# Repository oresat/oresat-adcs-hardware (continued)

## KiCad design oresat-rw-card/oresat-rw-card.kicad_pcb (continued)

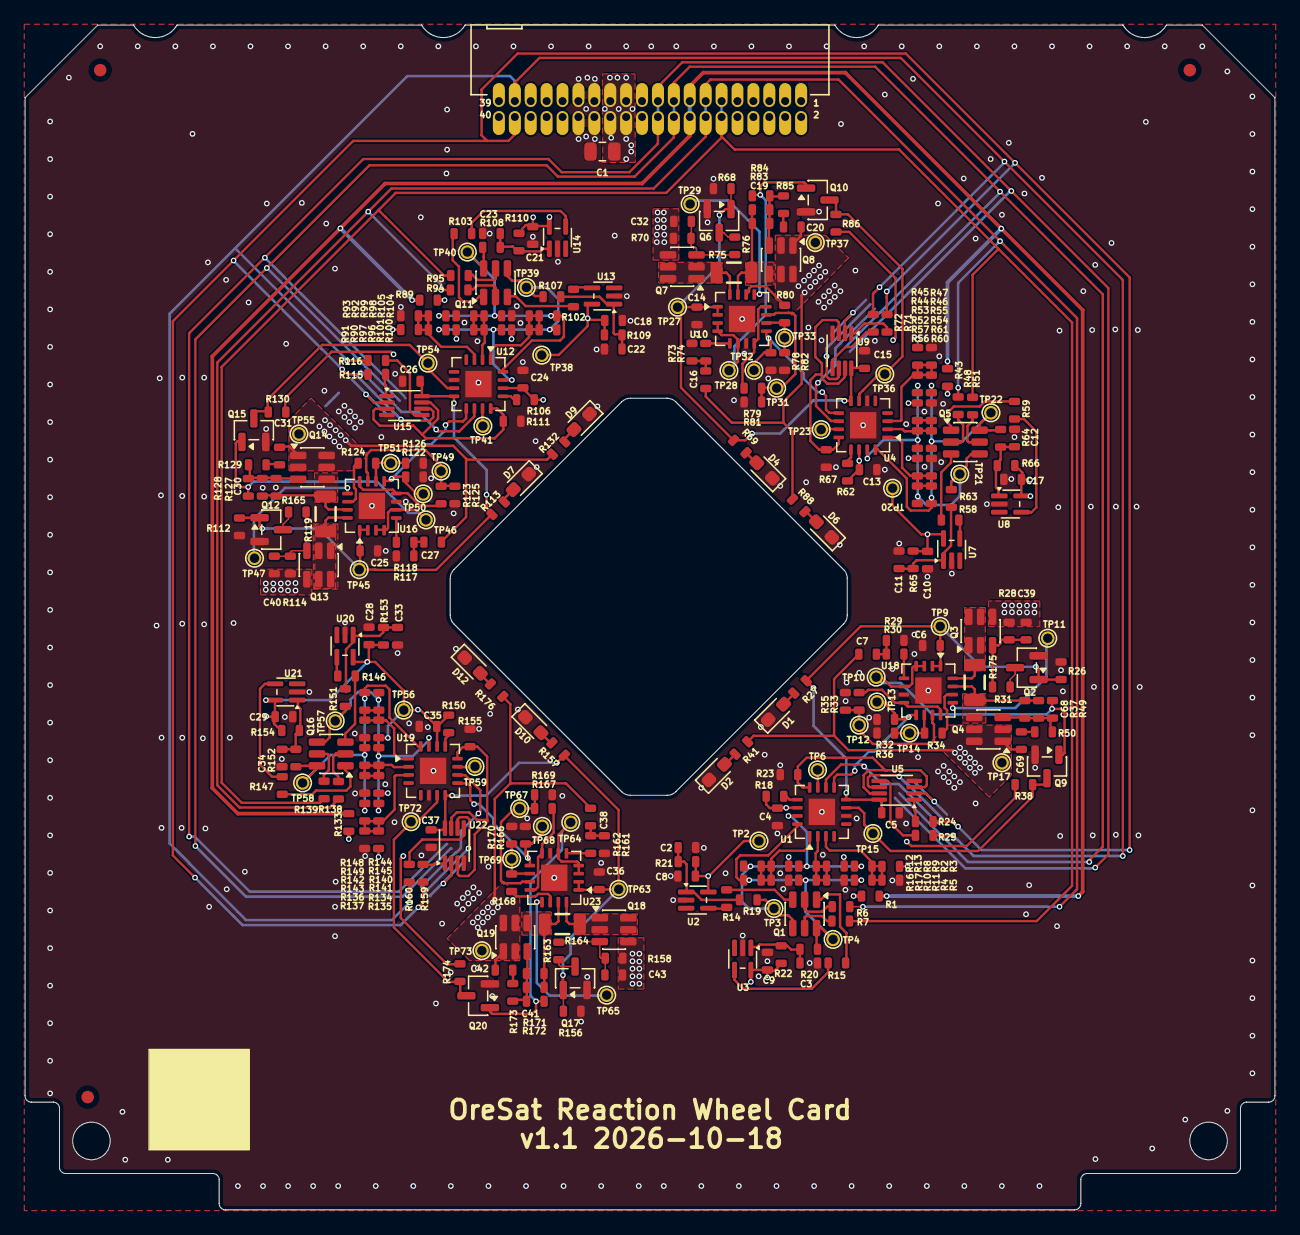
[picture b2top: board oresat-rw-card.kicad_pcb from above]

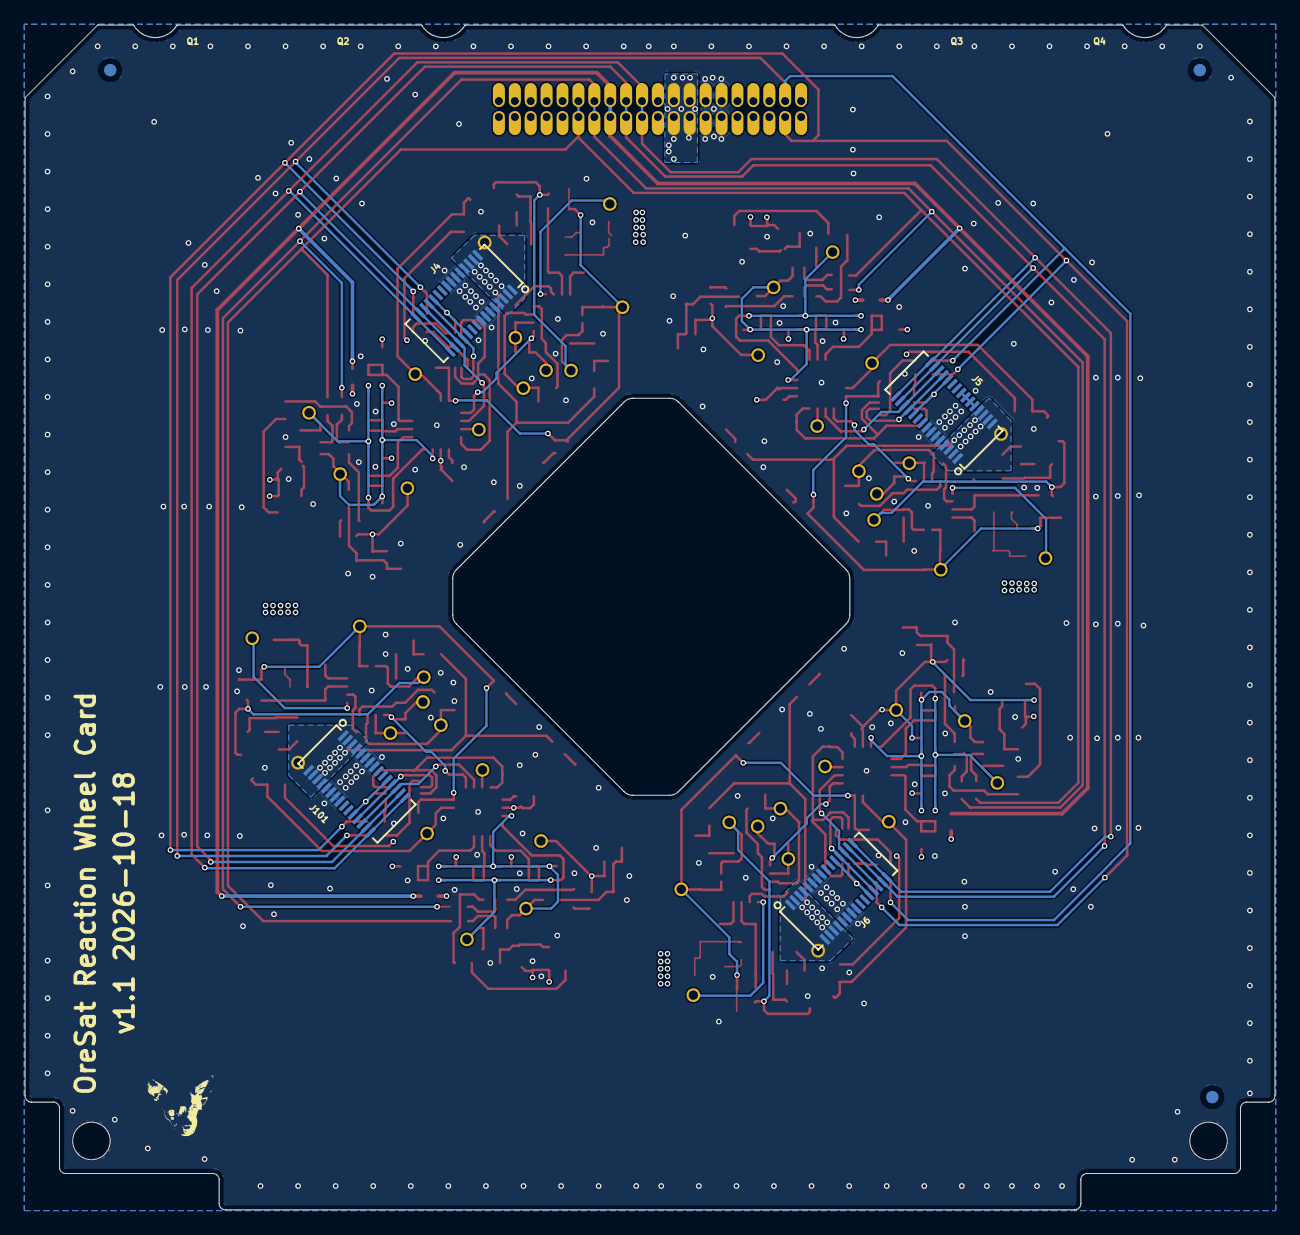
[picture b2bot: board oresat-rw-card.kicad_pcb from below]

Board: 4 copper layers, 99.8 x 94.6 mm, 321 parts (7 on the bottom side), 178 nets.

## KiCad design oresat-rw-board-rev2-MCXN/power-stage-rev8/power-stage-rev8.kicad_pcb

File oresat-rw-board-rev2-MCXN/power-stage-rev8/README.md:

---
title: "**MCXN-Reaction-Wheel-Board-V2**"
subtitle: |
  **Fabrication and Assembly Information**\
  For build TIME-STAMP
fontsize: 10pt
geometry:
  - margin=0.5in
toc: true
toc-depth: 2
colorlinks: true
urlcolor: blue
---

\newpage

# About this Board

## Board Description

The MCXN-Reaction-Wheel-Board-V2 is the dedicated controller board for the reaction wheel assembly. Each controller manages a single reaction wheel. Centered around the NXP MCXN947VDFT microcontroller, this board combines:

- GaN H-bridge inverters for motor driving
- Current sense amplifiers
- Encoder interfacing
- Additional thermal and voltage metrology
- Communication to the ADCS Card

## Documentation Links

- ADCS hardware Git repository: <https://github.com/oresat/oresat-adcs-hardware>

## Documentation Files

| Filename                        | Notes                                    |
| ------------------------------- | ---------------------------------------- |
| README.pdf                      | This README file                         |
| PROJECT-NAME-outline.dxf        | Board outline (with holes) in DXF format |
| PROJECT-NAME-pcba.step          | 3D model of PCBA (with components)       |
| PROJECT-NAME-render-top.jpg     | Render of the top of the 3D model        |
| PROJECT-NAME-render-bot.jpg     | Render of the bottom of the 3D model     |
| PROJECT-NAME-schematic.pdf      | PDF of board schematics                  |

## Board Renders

{width=50%}
{width=50%}

\newpage

# Printed Circuit Board (PCB) Fabrication Information

## Board Info

- 6-layer board
- Bounding box is approximately 50 x 33.5 mm 
- Board thickness is 1.6 mm 
- **Important:** See Materials section below
- 
## Board Requirements

- Design Rules
    - Minimum Trace width: 0.1 mm
    - Minimum Clearance/Space: 0.1 mm
- Drills and Vias
   - Via Diameter: 0.20 mm
   - Minimum Annular Width: 0.07 mm
- Outline/Routing
  - Requires a routing bit suitable for the 50x33.5mm profile.
- If not otherwise specified, build to IPC 6012 Class 2 or better. High precision is required across all fabrication steps.

## Materials

- Dielectric Material: Standard FR4
- Board Surface Treatment: ENIG (Electroless Nickel Immersion Gold)
- Controlled Impedance: None required

## Fabrication Files

### IPC-2581 File

| Filename                 | Notes                                   |
| ------------------------ | --------------------------------------- |
| PROJECT-NAME-ipc2581.xml | IPC-2581 board information file         |

### Legacy PCB Files (Gerbers/Drills)

| Filename                      | Notes                                         |
| ------------------------------| --------------------------------------------- |
| PROJECT-NAME-Edge_Cuts.gbr    | RS274X file for the dimension (outline) layer |
| PROJECT-NAME-F_Silkscreen.gbr | RS274X file for the top silkscreen            |
| PROJECT-NAME-F_Mask.gbr       | RS274X file for the top soldermask            |
| PROJECT-NAME-F_Cu.gbr         | RS274X file for the top copper layer          |
| PROJECT-NAME-In1_Cu.gbr       | RS274X file for the layer 2 copper            |
| PROJECT-NAME-In2_Cu.gbr       | RS274X file for the layer 3 copper            |
| PROJECT-NAME-In3_Cu.gbr       | RS274X file for the layer 4 copper            |
| PROJECT-NAME-In4_Cu.gbr       | RS274X file for the layer 5 copper            |
| PROJECT-NAME-B_Cu.gbr         | RS274X file for the bottom copper layer       |
| PROJECT-NAME-B_Mask.gbr       | RS274X file for the bottom soldermask         |
| PROJECT-NAME-B_Silkscreen.gbr | RS274X file for the bottom silkscreen         |
| PROJECT-NAME-NPTH.drl         | Excellon file for non-plated through holes    |
| PROJECT-NAME-PTH.drl          | Excellon file for plated through holes        | 

\newpage

# Printed Circuit Board Assembly (PCBA) Information

## Assembly Info

- Double-sided assembly (components on both Top and Bottom sides).
- Exclusively Surface Mount Technology (SMT) components; no Through-Hole (THT) parts.

## Assembly Requirements

- **Precision:** Extreme precision is required for all placement and reflow operations due to the density and component types (GaN, MCXN947VDFT).
- Assemble to IPC Class 2 or better.
- Solder paste **MUST** be leaded.
- Aqueous flux and wash strongly preferred.
   - Clean to NASA Standard "Visibly Clean (VC)": No particles or residues are visible to the naked eye.
- Ship in antistatic protective bags.

## Assembly Files

### IPC-2581 File

| Filename                 | Notes                           |
| ------------------------ | ------------------------------- |
| PROJECT-NAME-ipc2581.xml | IPC-2581 board information file |

### Bill of Materials (BOM)

| Filename             | Description                            |
| -------------------- | -------------------------------------- |
| PROJECT-NAME-bom.csv | BOM in Comma Separated Variable format |

### Solder Paste Stencils

| Filename                 | Notes                                            |
| ------------------------ | ------------------------------------------------ |
| PROJECT-NAME-B_Paste.gbr | RS274X file for bottom/back solder paste stencil |
| PROJECT-NAME-F_Paste.gbr | RS274X file for top/front solder paste stencil   |

### Mounting/Placement Location

| Filename            | Description                                 |
| ------------------- | ------------------------------------------- |
| PROJECT-NAME.pos    | Pick and place locations for components     |

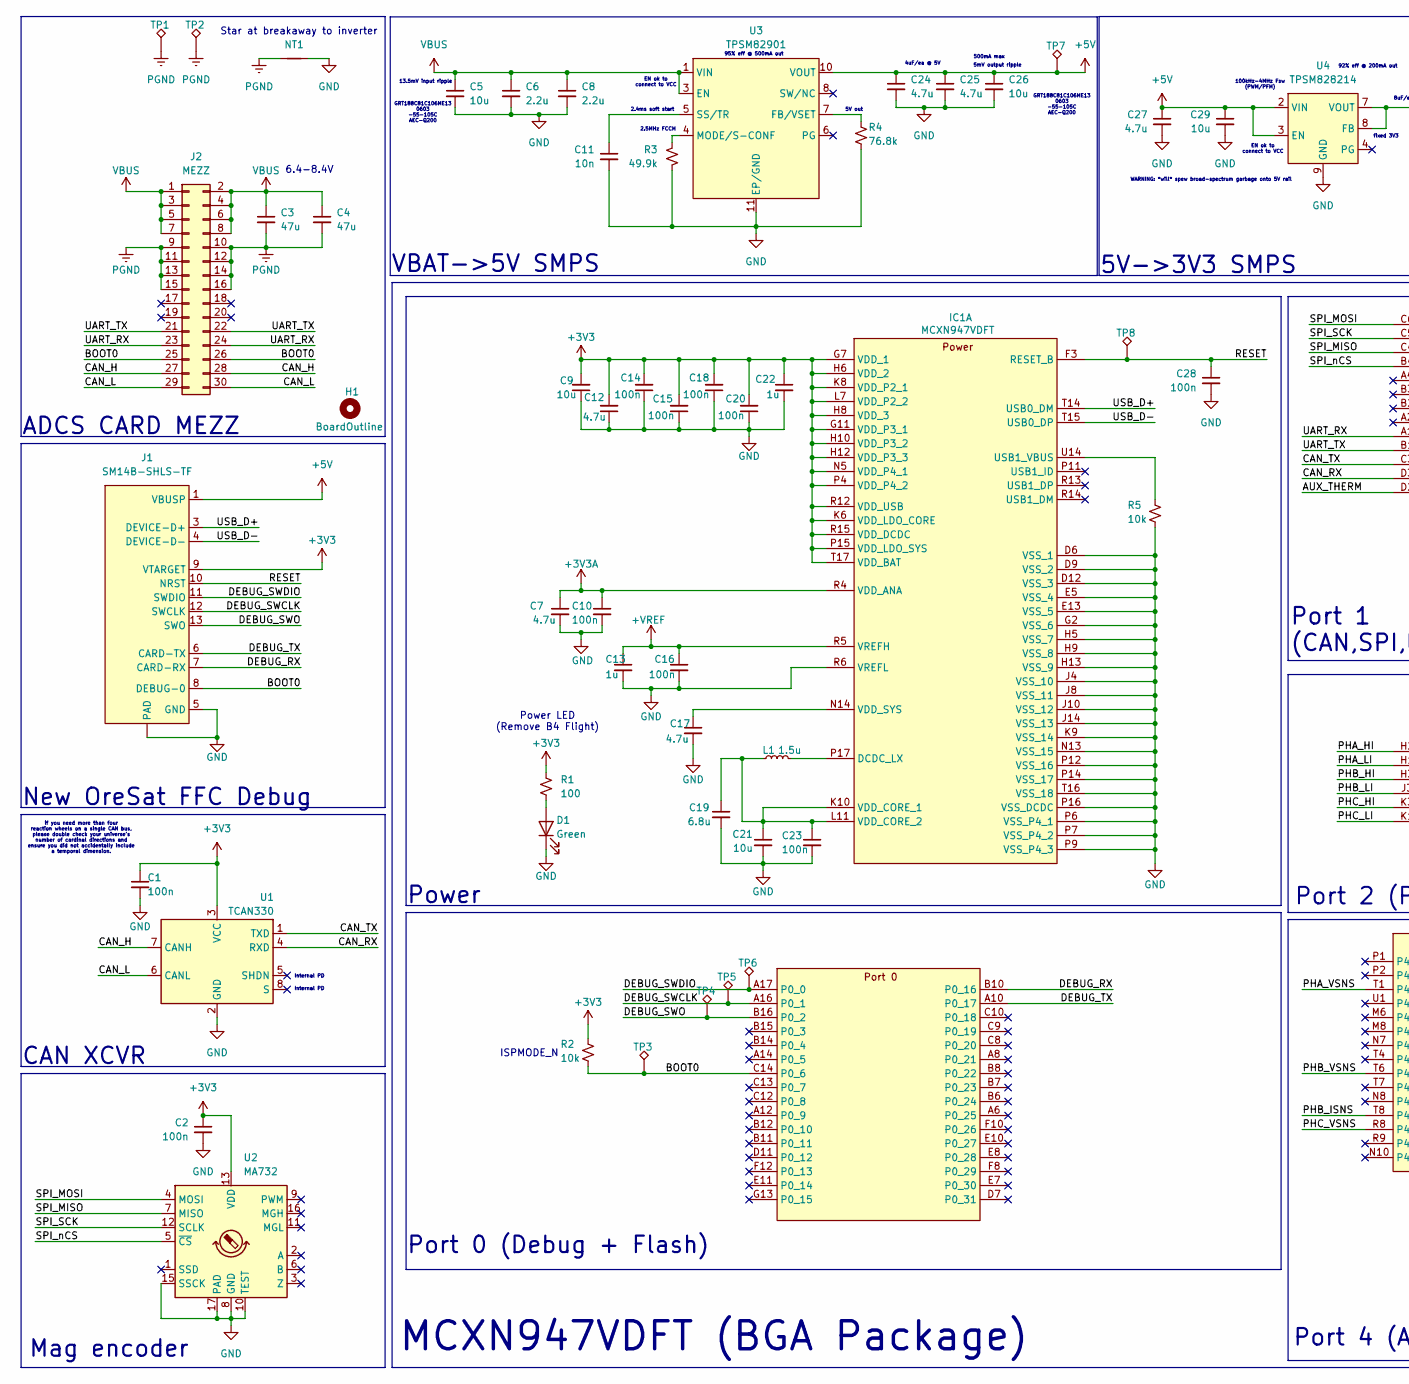
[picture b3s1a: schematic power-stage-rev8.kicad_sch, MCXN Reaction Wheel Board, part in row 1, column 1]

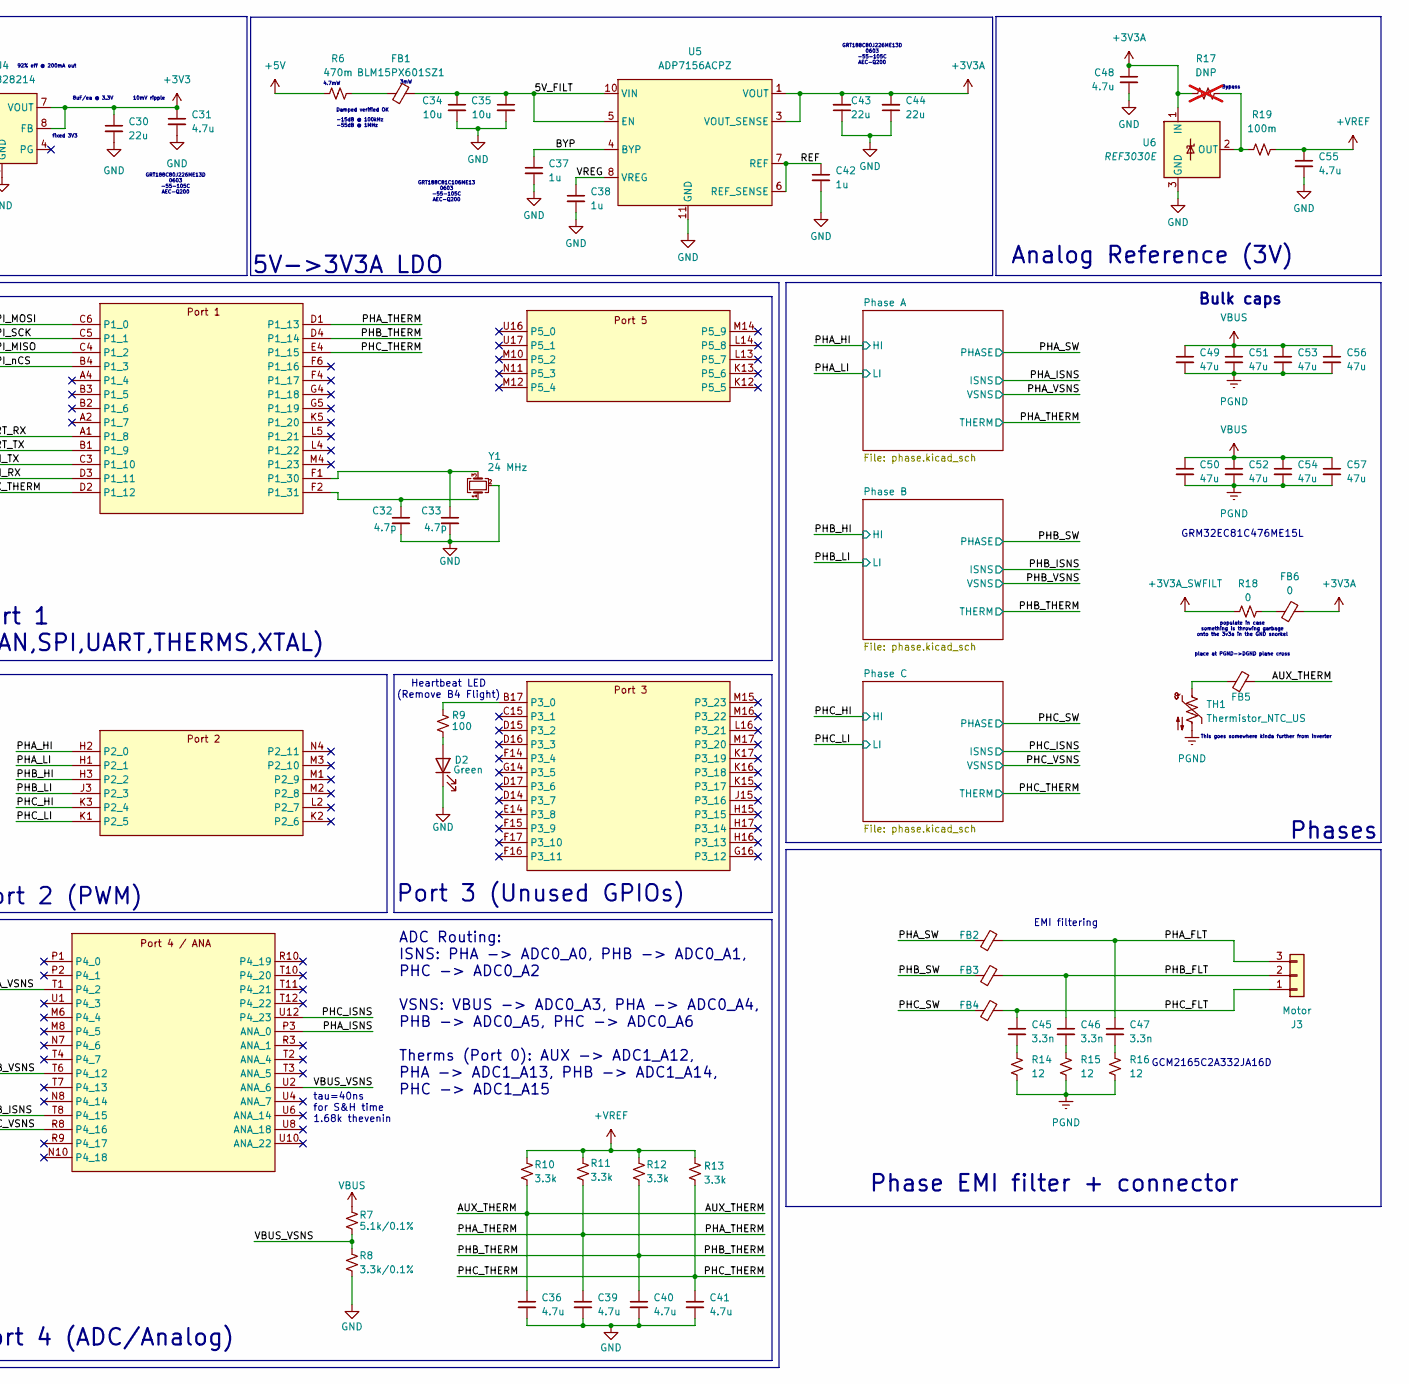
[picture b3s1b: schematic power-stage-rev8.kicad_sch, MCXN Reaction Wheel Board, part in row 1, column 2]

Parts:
C1, C2, C10, C14, C15, C16, C18, C20, C23, C28: 100n; C_0402_1005Metric; MPN GRT155R71E104KE01J
C3, C4, C49, C50, C51, C52, C53, C54, C56, C57: 47u; C_1210_3225Metric; MPN GRT32EC81C476KE13L
C5, C9, C21, C26, C29, C34, C35: 10u; C_0603_1608Metric; MPN GRT188C81C106ME13D
C6, C8: 2.2u; C_0402_1005Metric; MPN GRT155C81C225ME13D
C7, C12, C17, C24, C25, C27, C31, C36, C39, C40, C41, C48, C55: 4.7u; C_0402_1005Metric; MPN GRT155C81A475ME13J
C11: 10n; C_0402_1005Metric; MPN GCM155R71H103KA55D
C13, C22, C37, C38, C42: 1u; C_0402_1005Metric; MPN GRT155C81A105ME01D
C19: 6.8u; C_1206_3216Metric; MPN CGA5L1X7R1C685M160AC
C30, C43, C44: 22u; C_0603_1608Metric; MPN GRT188C80J226ME13D
C32, C33: 4.7p; C_0603_1608Metric; MPN GRM1885C1H4R7WA01D
C45, C46, C47: 3.3n; C_0805_2012Metric; MPN GCM2165C2A332JA16D
D1, D2: Green; LED_0603_1608Metric; MPN 150060VS55040
FB1, FB5: BLM15PX601SZ1; L_0402_1005Metric; MPN BLM15PX601SZ1D
FB2, FB3, FB4: BLM31SN500SN1L; L_1206_3216Metric; MPN BLM31SN500SN1L
FB6: 0; L_0402_1005Metric; MPN AC0402FR-070RL
H1: BoardOutline; board_def_rev8.0
IC1: MCXN947VDFT; BGA184C50P17X17_900X900X98; Manufacturer_Part_Number MCXN947VDFT
J1: SM14B-SHLS-TF; J-JST-SM14BSHLSTF; MPN SM14B-SHLS-TF
J2: MEZZ; 0555600307; MPN 0555600307
J3: Motor; Molex_Micro-Fit_3.0_43650-0315_1x03_P3.00mm_Vertical
L1: 1.5u; L_0805_2012Metric; MPN SRP2012TMA-1R5M
NT1: NetTie_2; NetTie-2_SMD_Pad2.0mm
R1, R9: 100; R_0402_1005Metric; MPN SR0402FR-7T100RL
R2, R5: 10k; R_0402_1005Metric; MPN AC0402DR-0710KL
R3: 49.9k; R_0402_1005Metric; MPN AC0402FR-0749K9L
R4: 76.8k; R_0402_1005Metric; MPN AC0402FR-0776K8L
R6: 470m; R_0402_1005Metric; MPN PE0402FRF7W0R47L
R7: 5.1k/0.1%; R_0402_1005Metric; MPN RP0402BRD075K1L
R8: 3.3k/0.1%; R_0402_1005Metric; MPN RP0402BRD073K3L
R10, R11, R12, R13: 3.3k; R_0402_1005Metric; MPN AC0402FR-073K3L
R14, R15, R16: 12; R_0805_2012Metric; MPN SR0805FR-7T12RL
R17: DNP; R_0402_1005Metric; MPN AC0402FR-070RL; not fitted
R18: 0; R_0402_1005Metric; MPN AC0402FR-070RL
R19: 100m; R_0402_1005Metric; MPN PE0402FRF470R1L
TH1: Thermistor_NTC_US; R_0402_1005Metric; MPN NCU15XH103F6SRC
TP1, TP2, TP3, TP4, TP5, TP6, TP7, TP8: TestPoint_Alt; TestPoint_Pad_1.0x1.0mm_NoSilk
U1: TCAN330; SOT-23-8; MPN TCAN330DCNR
U2: MA732; QFN-16-1EP_3x3mm_P0.5mm_EP1.75x1.75mm; MPN MA732GQ-Z
U3: TPSM82901; TI_uSIP_SIS; MPN TPSM82901SISR
U4: TPSM828214; TI_uSIP_SIL; MPN TPSM828214SILR
U5: ADP7156ACPZ; DFN-10-1EP_3x3mm_P0.5mm_EP1.65x2.38mm; MPN ADP7156ACPZ-3.3-R7
U6: REF3030E; SOT-23; MPN REF3030AIDBZT
Y1: 24 MHz; Crystal_SMD_2016-4Pin_2.0x1.6mm; MPN 830108212309

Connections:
+3V3: C1.1, C2.1, C9.2, C12.2, C14.2, C15.2, C18.2, C20.2, C22.1, C30.1, C31.1, IC1.G7 (VDD_1), IC1.G11 (VDD_P3_1), IC1.H6 (VDD_2), IC1.H8 (VDD_3), IC1.H10 (VDD_P3_2), IC1.H12 (VDD_P3_3), IC1.K6 (VDD_LDO_CORE), IC1.K8 (VDD_P2_1), IC1.L7 (VDD_P2_2), IC1.N5 (VDD_P4_1), IC1.P4 (VDD_P4_2), IC1.P15 (VDD_LDO_SYS), IC1.R12 (VDD_USB), IC1.R15 (VDD_DCDC), IC1.T17 (VDD_BAT), J1.9 (VTARGET), R1.1, R2.1, U1.3 (VCC), U2.13 (VDD), U4.5 (VOUT), U4.6 (VOUT), U4.7 (VOUT), U4.8 (FB)
+3V3A: C7.1, C10.1, C43.2, C44.2, C48.1, FB6.2, IC1.R4 (VDD_ANA), R17.1, U5.1 (VOUT), U5.2 (VOUT), U5.3 (VOUT_SENSE), U6.1 (IN)
+3V3A_SWFILT: R18.1; also elsewhere on the board
+5V: C24.1, C25.1, C26.1, C27.1, C29.1, J1.1 (VBUSP), J1.2 (VBUSP), R6.1, TP7.1 (1_1), U3.9 (VOUT), U3.10 (VOUT), U4.1 (VIN), U4.2 (VIN), U4.3 (EN); also elsewhere on the board
+VREF: C13.1, C16.1, C55.1, IC1.R5 (VREFH), R10.1, R11.1, R12.1, R13.1, R19.2; also elsewhere on the board
/5V_FILT: C34.1, C35.1, FB1.2, U5.5 (EN), U5.9 (VIN), U5.10 (VIN)
/AUX_THERM: C36.1, FB5.2, IC1.D2 (P1_12), R10.2
/BOOT0: IC1.C14 (P0_6), J1.8 (DEBUG-0), J2.25, J2.26, R2.2, TP3.1 (1_1)
/BYP: C37.1, U5.4 (BYP)
/CAN_H: J2.27, J2.28, U1.7 (CANH)
/CAN_L: J2.29, J2.30, U1.6 (CANL)
/CAN_RX: IC1.D3 (P1_11), U1.4 (RXD)
/CAN_TX: IC1.C3 (P1_10), U1.1 (TXD)
/DEBUG_RX: IC1.B10 (P0_16), J1.7 (CARD-RX)
/DEBUG_SWCLK: IC1.A16 (P0_1), J1.12 (SWCLK), TP5.1 (1_1)
/DEBUG_SWDIO: IC1.A17 (P0_0), J1.11 (SWDIO), TP6.1 (1_1)
/DEBUG_SWO: IC1.B16 (P0_2), J1.13 (SWO), TP4.1 (1_1)
/DEBUG_TX: IC1.A10 (P0_17), J1.6 (CARD-TX)
/PHA_FLT: C47.1, FB2.2, J3.3
/PHA_HI: IC1.H2 (P2_0); also elsewhere on the board
/PHA_ISNS: IC1.P3 (ANA_0); also elsewhere on the board
/PHA_LI: IC1.H1 (P2_1); also elsewhere on the board
/PHA_SW: FB2.1; also elsewhere on the board
/PHA_THERM: C39.1, IC1.D1 (P1_13), R11.2; also elsewhere on the board
/PHA_VSNS: IC1.T1 (P4_2); also elsewhere on the board
/PHB_FLT: C46.1, FB3.2, J3.2
/PHB_HI: IC1.H3 (P2_2); also elsewhere on the board
/PHB_ISNS: IC1.T8 (P4_15); also elsewhere on the board
/PHB_LI: IC1.J3 (P2_3); also elsewhere on the board
/PHB_SW: FB3.1; also elsewhere on the board
/PHB_THERM: C40.1, IC1.D4 (P1_14), R12.2; also elsewhere on the board
/PHB_VSNS: IC1.T6 (P4_12); also elsewhere on the board
/PHC_FLT: C45.1, FB4.2, J3.1
/PHC_HI: IC1.K3 (P2_4); also elsewhere on the board
/PHC_ISNS: IC1.U12 (P4_23); also elsewhere on the board
/PHC_LI: IC1.K1 (P2_5); also elsewhere on the board
/PHC_SW: FB4.1; also elsewhere on the board
/PHC_THERM: C41.1, IC1.E4 (P1_15), R13.2; also elsewhere on the board
/PHC_VSNS: IC1.R8 (P4_16); also elsewhere on the board
/REF: C42.1, U5.6 (REF_SENSE), U5.7 (REF)
/RESET: C28.1, IC1.F3 (RESET_B), J1.10 (NRST), TP8.1 (1_1)
/SPI_MISO: IC1.C4 (P1_2), U2.7 (MISO)
/SPI_MOSI: IC1.C6 (P1_0), U2.4 (MOSI)
/SPI_SCK: IC1.C5 (P1_1), U2.12 (SCLK)
/SPI_nCS: IC1.B4 (P1_3), U2.5 (~CS)
/UART_RX: IC1.A1 (P1_8), J2.23, J2.24
/UART_TX: IC1.B1 (P1_9), J2.21, J2.22
/USB_D+: IC1.T14 (USB0_DM), J1.3 (DEVICE-D+)
/USB_D-: IC1.T15 (USB0_DP), J1.4 (DEVICE-D-)
/VBUS_VSNS: IC1.U2 (ANA_6), R7.2, R8.1
/VREG: C38.1, U5.8 (VREG)
GND: C1.2, C2.2, C5.2, C6.2, C7.2, C8.2, C9.1, C10.2, C11.2, C12.1, C13.2, C14.1, C15.1, C16.2, C17.2, C18.1, C19.2, C20.1, C21.2, C22.2, C23.2, C24.2, C25.2, C26.2, C27.2, C28.2, C29.2, C30.2, C31.2, C32.2, C33.2, C34.2, C35.2, C36.2, C37.2, C38.2, C39.2, C40.2, C41.2, C42.2, C43.1, C44.1, C48.2, C55.2, D1.1 (K), D2.1 (K), IC1.D6 (VSS_1), IC1.D9 (VSS_2), IC1.D12 (VSS_3), IC1.E5 (VSS_4), IC1.E13 (VSS_5), IC1.G2 (VSS_6), IC1.H5 (VSS_7), IC1.H9 (VSS_8), IC1.H13 (VSS_9), IC1.J4 (VSS_10), IC1.J8 (VSS_11), IC1.J10 (VSS_12), IC1.J14 (VSS_13), IC1.K9 (VSS_14), IC1.N13 (VSS_15), IC1.P6 (VSS_P4_1), IC1.P7 (VSS_P4_2), IC1.P9 (VSS_P4_3), IC1.P12 (VSS_16), IC1.P14 (VSS_17), IC1.P16 (VSS_DCDC), IC1.R6 (VREFL), IC1.T16 (VSS_18), J1.5 (GND), J1.14 (GND), J1.15 (PAD), J1.16 (PAD), NT1.2, R3.2, R4.2, R5.2, R8.2, U1.2 (GND), U2.8 (GND), U2.10 (TEST), U2.15 (SSCK), U2.17 (PAD), U3.11 (EP/GND), U4.9 (GND), U4.10 (GND), U5.11 (GND), U6.3 (GND), Y1.2 (G), Y1.4 (G); also elsewhere on the board
unnamed: C45.2, R14.1
unnamed: C46.2, R15.1
unnamed: C47.2, R16.1
unnamed: D1.2 (A), R1.2
unnamed: D2.2 (A), R9.2
unnamed: FB1.1, R6.2
unnamed: FB5.1, TH1.1
unnamed: FB6.1, R18.2
unnamed: IC1.P17 (DCDC_LX), L1.2
unnamed: IC1.U14 (USB1_VBUS), R5.1
unnamed: C19.1, C21.1, C23.1, IC1.K10 (VDD_CORE_1), IC1.L11 (VDD_CORE_2), L1.1
unnamed: C17.1, IC1.N14 (VDD_SYS)
unnamed: C33.1, IC1.F1 (P1_30), Y1.3
unnamed: C32.1, IC1.F2 (P1_31), Y1.1
unnamed: IC1.B17 (P3_0), R9.1
unnamed: R4.1, U3.7 (FB/VSET)
unnamed: R3.1, U3.4 (MODE/S-CONF)
unnamed: C11.1, U3.5 (SS/TR)
unnamed: R17.2, R19.1, U6.2 (OUT)
PGND: C3.2, C4.2, C49.2, C50.2, C51.2, C52.2, C53.2, C54.2, C56.2, C57.2, J2.9, J2.10, J2.11, J2.12, J2.13, J2.14, J2.15, J2.16, NT1.1, R14.2, R15.2, R16.2, TH1.2, TP1.1 (1_1), TP2.1 (1_1); also elsewhere on the board
VBUS: C3.1, C4.1, C5.1, C6.1, C8.1, C49.1, C50.1, C51.1, C52.1, C53.1, C54.1, C56.1, C57.1, J2.1, J2.2, J2.3, J2.4, J2.5, J2.6, J2.7, J2.8, R7.1, U3.1 (VIN), U3.2 (VIN), U3.3 (EN); also elsewhere on the board

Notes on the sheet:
MCXN947VDFT (BGA Package)
4.7mW
8uF/ea @ 3.3V
GRT188C81C106ME13 0603 -55-105C AEC-Q200
Bypass
-15dB @ 100kHz -55dB @ 1MHz
populate in case something is throwing garbage onto the 3v3a in the GND snorkel
place at PGND->DGND plane cross
3mW
Bulk caps
GRT188C80J226ME13D 0603 -55-105C AEC-Q200
VBAT->5V SMPS
500mA max
Port 1 (CAN,SPI,UART,THERMS,XTAL)
CAN XCVR
tau=40ns for S&H time
EN ok to connect to VCC
2.4ms soft start
5mV output ripple
Port 4 (ADC/Analog)
10mV ripple
Port 3 (Unused GPIOs)
ADCS CARD MEZZ
1.68k thevenin
Internal PD
This goes somewhere kinda further from inverter
if you need more than four reaction wheels on a single CAN bus, please double check your universe's number of cardinal directions and ensure you did not accidentally include a temporal dimension.
Mag encoder
Star at breakaway to inverter
EMI filtering
ISPMODE_N
Power LED (Remove B4 Flight)
100kHz-4MHz Fsw (PWM/PFM)
GRM32EC81C476ME15L
Damped verified OK
4uF/ea @ 5V
Phases
New OreSat FFC Debug
Heartbeat LED (Remove B4 Flight)
fixed 3V3

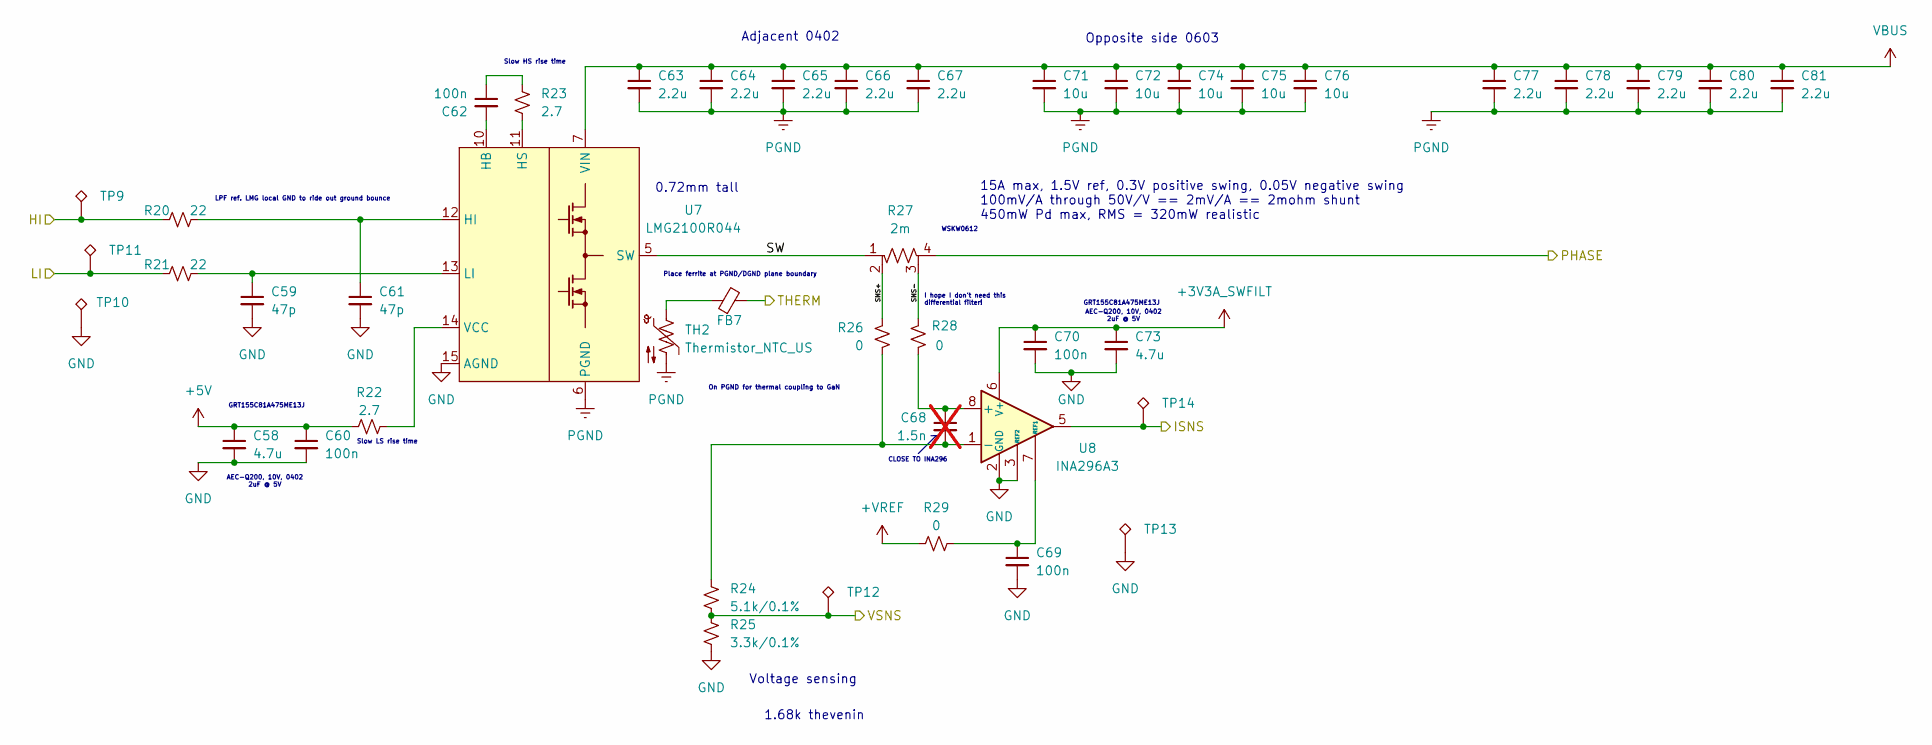
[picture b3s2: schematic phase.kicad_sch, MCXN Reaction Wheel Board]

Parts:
C58, C73: 4.7u; C_0402_1005Metric; MPN GRT155C81A475ME13J
C59, C61: 47p; C_0402_1005Metric; MPN GCM1555C1H470JA16D
C60, C62, C69, C70: 100n; C_0402_1005Metric; MPN GRT155R71E104KE01J
C63, C64, C65, C66, C67, C77, C78, C79, C80, C81: 2.2u; C_0402_1005Metric; MPN GRT155C81C225ME13D
C68: 1.5n; C_0402_1005Metric; MPN GCM155R71H152KA37D; not fitted
C71, C72, C74, C75, C76: 10u; C_0603_1608Metric; MPN GRT188C81C106ME13D
FB7: BLM15PX601SZ1; L_0402_1005Metric; MPN BLM15PX601SZ1D
R20, R21: 22; R_0402_1005Metric; MPN AC0402FR-0722RL
R22, R23: 2.7; R_0402_1005Metric; MPN AC0402FR-072R7L
R24: 5.1k/0.1%; R_0402_1005Metric; MPN RP0402BRD075K1L
R25: 3.3k/0.1%; R_0402_1005Metric; MPN RP0402BRD073K3L
R26, R28, R29: 0; R_0402_1005Metric; MPN AC0402FR-070RL
R27: 2m; R_Shunt_Vishay_WSKW0612; MPN WSKW06122L000FEA
TH2: Thermistor_NTC_US; R_0402_1005Metric; MPN NCU15XH103F6SRC
TP9, TP10, TP11, TP12, TP13, TP14: TestPoint_Alt; TestPoint_Pad_1.0x1.0mm_NoSilk
U7: LMG2100R044; TI_torment_nexus; MPN LMG2100R044RARR
U8: INA296A3; SOT-23-8; MPN INA296A3QDDFRQ1

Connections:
+3V3A_SWFILT: C70.1, C73.1, U8.6 (V+); also elsewhere on the board
+5V: C58.1, C60.1, R22.1; also elsewhere on the board
+VREF: R29.1; also elsewhere on the board
/PHA_HI: R20.2, TP9.1 (1_1); also elsewhere on the board
/PHA_ISNS: TP14.1 (1_1), U8.5; also elsewhere on the board
/PHA_LI: R21.1, TP11.1 (1_1); also elsewhere on the board
/PHA_SW: R27.4; also elsewhere on the board
/PHA_THERM: FB7.2; also elsewhere on the board
/PHA_VSNS: R24.2, R25.1, TP12.1 (1_1); also elsewhere on the board
/Phase A/SNS+: R26.1, R27.2
/Phase A/SNS-: R27.3, R28.2
/Phase A/SW: R27.1, U7.5 (SW)
GND: C58.2, C59.2, C60.2, C61.2, C69.2, C70.2, C73.2, R25.2, TP10.1 (1_1), TP13.1 (1_1), U7.15 (AGND), U8.2 (GND), U8.3 (REF2), U8.4 (GND); also elsewhere on the board
unnamed: C62.1, R23.1
unnamed: FB7.1, TH2.1
unnamed: C62.2, U7.10 (HB)
unnamed: C61.1, R20.1, U7.12 (HI)
unnamed: R23.2, U7.11 (HS)
unnamed: C59.1, R21.2, U7.13 (LI)
unnamed: R22.2, U7.14 (VCC)
unnamed: C68.1, R28.1, U8.8 (+)
unnamed: C68.2, R24.1, R26.2, U8.1 (-)
unnamed: C69.1, R29.2, U8.7 (REF1)
PGND: C63.2, C64.2, C65.2, C66.2, C67.2, C71.2, C72.2, C74.2, C75.2, C76.2, C77.2, C78.2, C79.2, C80.2, C81.2, TH2.2, U7.6 (PGND), U7.17 (PGND); also elsewhere on the board
VBUS: C63.1, C64.1, C65.1, C66.1, C67.1, C71.1, C72.1, C74.1, C75.1, C76.1, C77.1, C78.1, C79.1, C80.1, C81.1, U7.7 (VIN); also elsewhere on the board

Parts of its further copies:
C82, C97, C106, C121: 4.7u; C_0402_1005Metric; MPN GRT155C81A475ME13J
C83, C85, C107, C109: 47p; C_0402_1005Metric; MPN GCM1555C1H470JA16D
C84, C86, C93, C94, C108, C110, C117, C118: 100n; C_0402_1005Metric; MPN GRT155R71E104KE01J
C87, C88, C89, C90, C91, C101, C102, C103, C104, C105, C111, C112, C113, C114, C115, C125, C126, C127, C128, C129: 2.2u; C_0402_1005Metric; MPN GRT155C81C225ME13D
C92, C116: 1.5n; C_0402_1005Metric; MPN GCM155R71H152KA37D; not fitted
C95, C96, C98, C99, C100, C119, C120, C122, C123, C124: 10u; C_0603_1608Metric; MPN GRT188C81C106ME13D
FB8, FB9: BLM15PX601SZ1; L_0402_1005Metric; MPN BLM15PX601SZ1D
R30, R31, R40, R41: 22; R_0402_1005Metric; MPN AC0402FR-0722RL
R32, R33, R42, R43: 2.7; R_0402_1005Metric; MPN AC0402FR-072R7L
R34, R44: 5.1k/0.1%; R_0402_1005Metric; MPN RP0402BRD075K1L
R35, R45: 3.3k/0.1%; R_0402_1005Metric; MPN RP0402BRD073K3L
R36, R38, R39, R46, R48, R49: 0; R_0402_1005Metric; MPN AC0402FR-070RL
R37, R47: 2m; R_Shunt_Vishay_WSKW0612; MPN WSKW06122L000FEA
TH3, TH4: Thermistor_NTC_US; R_0402_1005Metric; MPN NCU15XH103F6SRC
TP15, TP16, TP17, TP18, TP19, TP20, TP21, TP22, TP23, TP24, TP25, TP26: TestPoint_Alt; TestPoint_Pad_1.0x1.0mm_NoSilk
U9, U11: LMG2100R044; TI_torment_nexus; MPN LMG2100R044RARR
U10, U12: INA296A3; SOT-23-8; MPN INA296A3QDDFRQ1

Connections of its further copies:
+3V3A_SWFILT: C94.1, C97.1, C118.1, C121.1, U10.6 (V+), U12.6 (V+); also elsewhere on the board
+5V: C82.1, C84.1, C106.1, C108.1, R32.1, R42.1; also elsewhere on the board
+VREF: R39.1, R49.1; also elsewhere on the board
/PHB_HI: R30.2, TP15.1 (1_1); also elsewhere on the board
/PHB_ISNS: TP20.1 (1_1), U10.5; also elsewhere on the board
/PHB_LI: R31.1, TP17.1 (1_1); also elsewhere on the board
/PHB_SW: R37.4; also elsewhere on the board
/PHB_THERM: FB8.2; also elsewhere on the board
/PHB_VSNS: R34.2, R35.1, TP18.1 (1_1); also elsewhere on the board
/PHC_HI: R40.2, TP21.1 (1_1); also elsewhere on the board
/PHC_ISNS: TP26.1 (1_1), U12.5; also elsewhere on the board
/PHC_LI: R41.1, TP23.1 (1_1); also elsewhere on the board
/PHC_SW: R47.4; also elsewhere on the board
/PHC_THERM: FB9.2; also elsewhere on the board
/PHC_VSNS: R44.2, R45.1, TP24.1 (1_1); also elsewhere on the board
/Phase B/SNS+: R36.1, R37.2
/Phase B/SNS-: R37.3, R38.2
/Phase B/SW: R37.1, U9.5 (SW)
/Phase C/SNS+: R46.1, R47.2
/Phase C/SNS-: R47.3, R48.2
/Phase C/SW: R47.1, U11.5 (SW)
GND: C82.2, C83.2, C84.2, C85.2, C93.2, C94.2, C97.2, C106.2, C107.2, C108.2, C109.2, C117.2, C118.2, C121.2, R35.2, R45.2, TP16.1 (1_1), TP19.1 (1_1), TP22.1 (1_1), TP25.1 (1_1), U9.15 (AGND), U10.2 (GND), U10.3 (REF2), U10.4 (GND), U11.15 (AGND), U12.2 (GND), U12.3 (REF2), U12.4 (GND); also elsewhere on the board
unnamed: C86.1, R33.1
unnamed: C110.1, R43.1
unnamed: FB8.1, TH3.1
unnamed: FB9.1, TH4.1
unnamed: C86.2, U9.10 (HB)
unnamed: C85.1, R30.1, U9.12 (HI)
unnamed: R33.2, U9.11 (HS)
unnamed: C83.1, R31.2, U9.13 (LI)
unnamed: R32.2, U9.14 (VCC)
unnamed: C92.1, R38.1, U10.8 (+)
unnamed: C92.2, R34.1, R36.2, U10.1 (-)
unnamed: C93.1, R39.2, U10.7 (REF1)
unnamed: C110.2, U11.10 (HB)
unnamed: C109.1, R40.1, U11.12 (HI)
unnamed: R43.2, U11.11 (HS)
unnamed: C107.1, R41.2, U11.13 (LI)
unnamed: R42.2, U11.14 (VCC)
unnamed: C116.1, R48.1, U12.8 (+)
unnamed: C116.2, R44.1, R46.2, U12.1 (-)
unnamed: C117.1, R49.2, U12.7 (REF1)
PGND: C87.2, C88.2, C89.2, C90.2, C91.2, C95.2, C96.2, C98.2, C99.2, C100.2, C101.2, C102.2, C103.2, C104.2, C105.2, C111.2, C112.2, C113.2, C114.2, C115.2, C119.2, C120.2, C122.2, C123.2, C124.2, C125.2, C126.2, C127.2, C128.2, C129.2, TH3.2, TH4.2, U9.6 (PGND), U9.17 (PGND), U11.6 (PGND), U11.17 (PGND); also elsewhere on the board
VBUS: C87.1, C88.1, C89.1, C90.1, C91.1, C95.1, C96.1, C98.1, C99.1, C100.1, C101.1, C102.1, C103.1, C104.1, C105.1, C111.1, C112.1, C113.1, C114.1, C115.1, C119.1, C120.1, C122.1, C123.1, C124.1, C125.1, C126.1, C127.1, C128.1, C129.1, U9.7 (VIN), U11.7 (VIN); also elsewhere on the board

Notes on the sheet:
0.72mm tall
I hope I don't need this differential filter!
On PGND for thermal coupling to GaN
1.68k thevenin
Opposite side 0603
Adjacent 0402
WSKW0612
GRT155C81A475ME13J
Slow HS rise time
Voltage sensing
AEC-Q200, 10V, 0402 2uF @ 5V
Place ferrite at PGND/DGND plane boundary
Slow LS rise time
LPF ref. LMG local GND to ride out ground bounce
CLOSE TO INA296
15A max, 1.5V ref, 0.3V positive swing, 0.05V negative swing 100mV/A through 50V/V == 2mV/A == 2mohm shunt 450mW Pd max, RMS = 320mW realistic

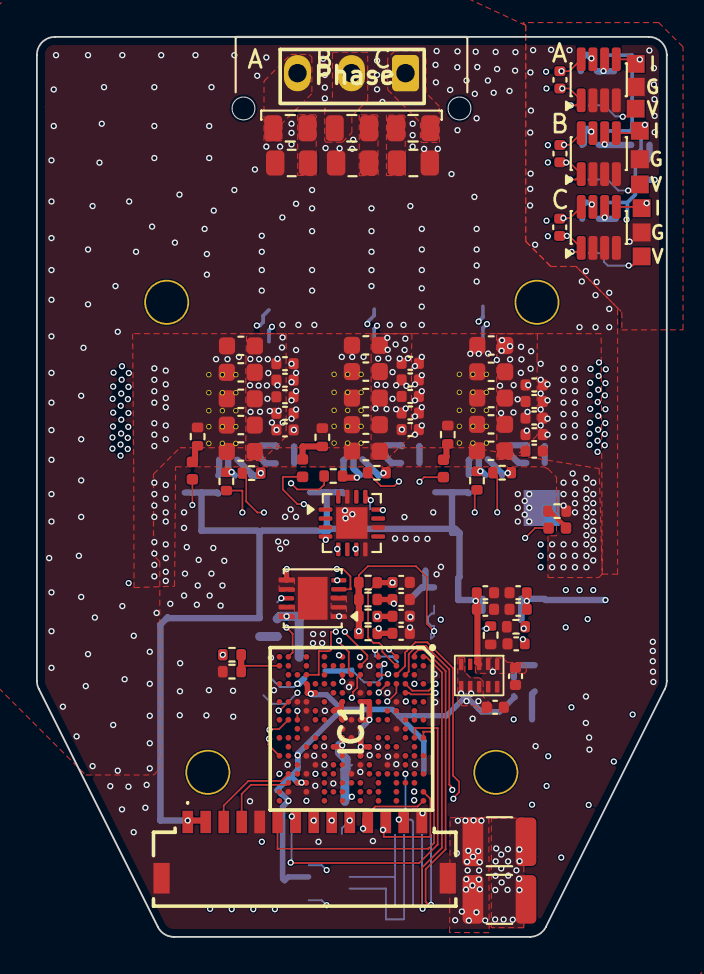
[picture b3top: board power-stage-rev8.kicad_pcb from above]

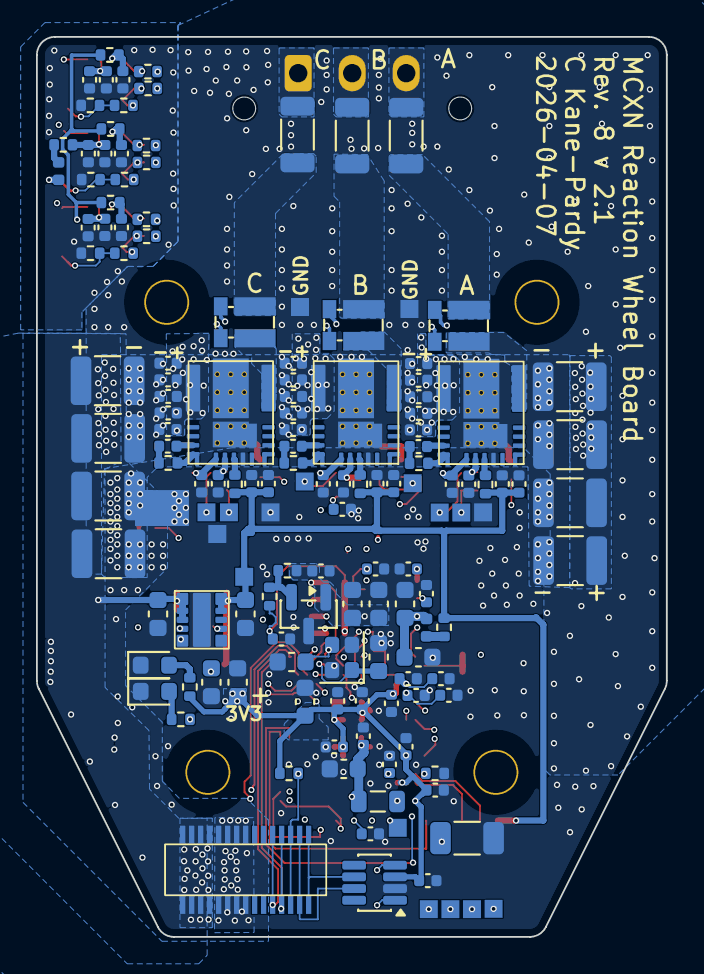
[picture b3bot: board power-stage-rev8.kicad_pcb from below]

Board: 6 copper layers, 35.0 x 50.0 mm, 239 parts (146 on the bottom side), 112 nets.

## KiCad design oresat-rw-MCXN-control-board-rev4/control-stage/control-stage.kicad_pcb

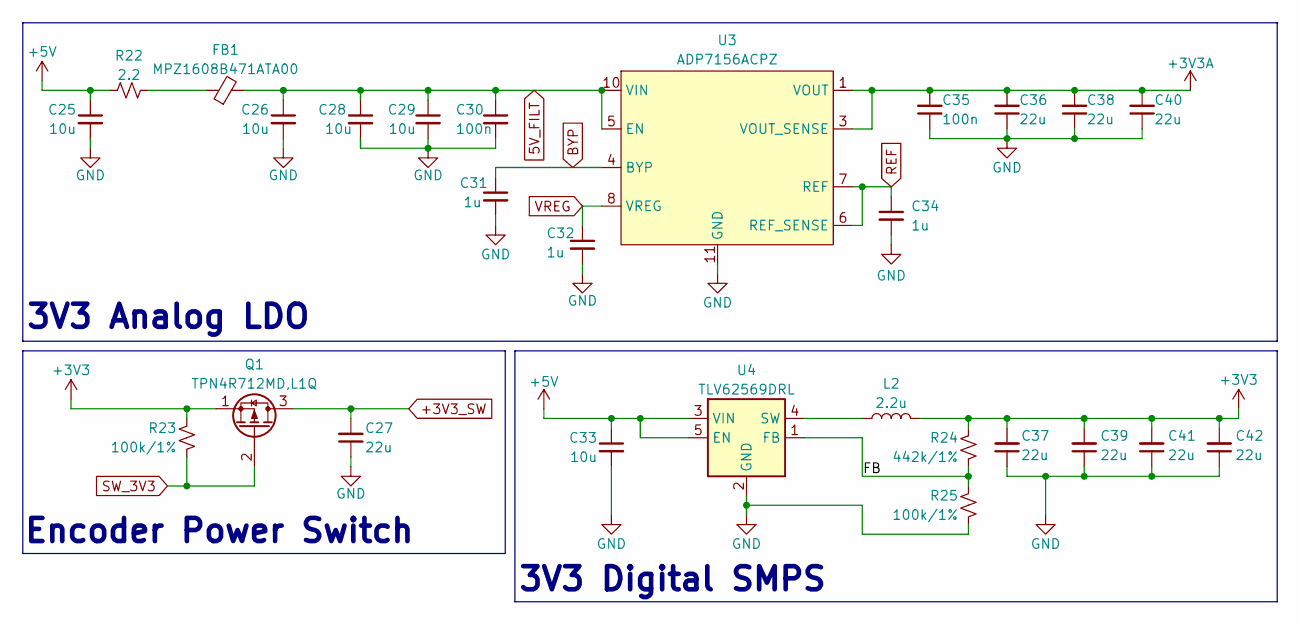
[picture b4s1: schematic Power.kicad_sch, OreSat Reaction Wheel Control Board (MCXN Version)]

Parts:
C25, C26, C28, C29, C33: 10u; C_0603_1608Metric; Mfg P/N GRM188R61A106KE69J
C27, C36, C37, C38, C39, C40, C41, C42: 22u; C_0603_1608Metric; Mfg P/N GRM188R61A226ME15D
C30, C35: 100n; C_0402_1005Metric; Mfg P/N GRM155R61A104KA01J
C31, C32, C34: 1u; C_0402_1005Metric; Mfg P/N GRT155R61A105KE01D
FB1: MPZ1608B471ATA00; L_0603_1608Metric; Mfg P/N MPZ1608B471ATA00
L2: 2.2u; L_1008_2520Metric; Mfg P/N DFE252012PD-2R2M=P2
Q1: TPN4R712MD,L1Q; TSON-Advance; Mfg P/N TPN4R712MD,L1Q
R22: 2.2; R_0603_1608Metric; Mfg P/N AF0603FR-072R2L
R23, R25: 100k/1%; R_0402_1005Metric; Mfg P/N AC0402FR-13100KL
R24: 442k/1%; R_0402_1005Metric; Mfg P/N RMCF0402FT442K
U3: ADP7156ACPZ; DFN-10-1EP_3x3mm_P0.5mm_EP1.65x2.38mm; Mfg P/N ADP7156ACPZ-3.3-R7
U4: TLV62569DRL; SOT-563; Mfg P/N TLV62569ADRLR

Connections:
5V_FILT: C26.1, C28.1, C29.1, C30.1, FB1.2, U3.5 (EN), U3.9 (VIN), U3.10 (VIN)
+3V3: C37.2, C39.2, C41.2, C42.2, L2.2, Q1.1 (S), R23.2, R24.2; also elsewhere on the board
+3V3A: C35.2, C36.2, C38.2, C40.2, U3.1 (VOUT), U3.2 (VOUT), U3.3 (VOUT_SENSE); also elsewhere on the board
+3V3_SW: C27.2, Q1.3 (D); also elsewhere on the board
+5V: C25.1, C33.1, R22.1, U4.3 (VIN), U4.5 (EN); also elsewhere on the board
/Power Architecture/FB: R24.1, R25.2, U4.1 (FB)
BYP: C31.1, U3.4 (BYP)
GND: C25.2, C26.2, C27.1, C28.2, C29.2, C30.2, C31.2, C32.2, C33.2, C34.2, C35.1, C36.1, C37.1, C38.1, C39.1, C40.1, C41.1, C42.1, R25.1, U3.11 (GND), U4.2 (GND); also elsewhere on the board
unnamed: FB1.1, R22.2
unnamed: L2.1, U4.4 (SW)
REF: C34.1, U3.6 (REF_SENSE), U3.7 (REF)
SW_3V3: Q1.2 (G), R23.1; also elsewhere on the board
VREG: C32.1, U3.8 (VREG)

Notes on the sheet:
3V3 Digital SMPS
3V3 Analog LDO
Encoder Power Switch
